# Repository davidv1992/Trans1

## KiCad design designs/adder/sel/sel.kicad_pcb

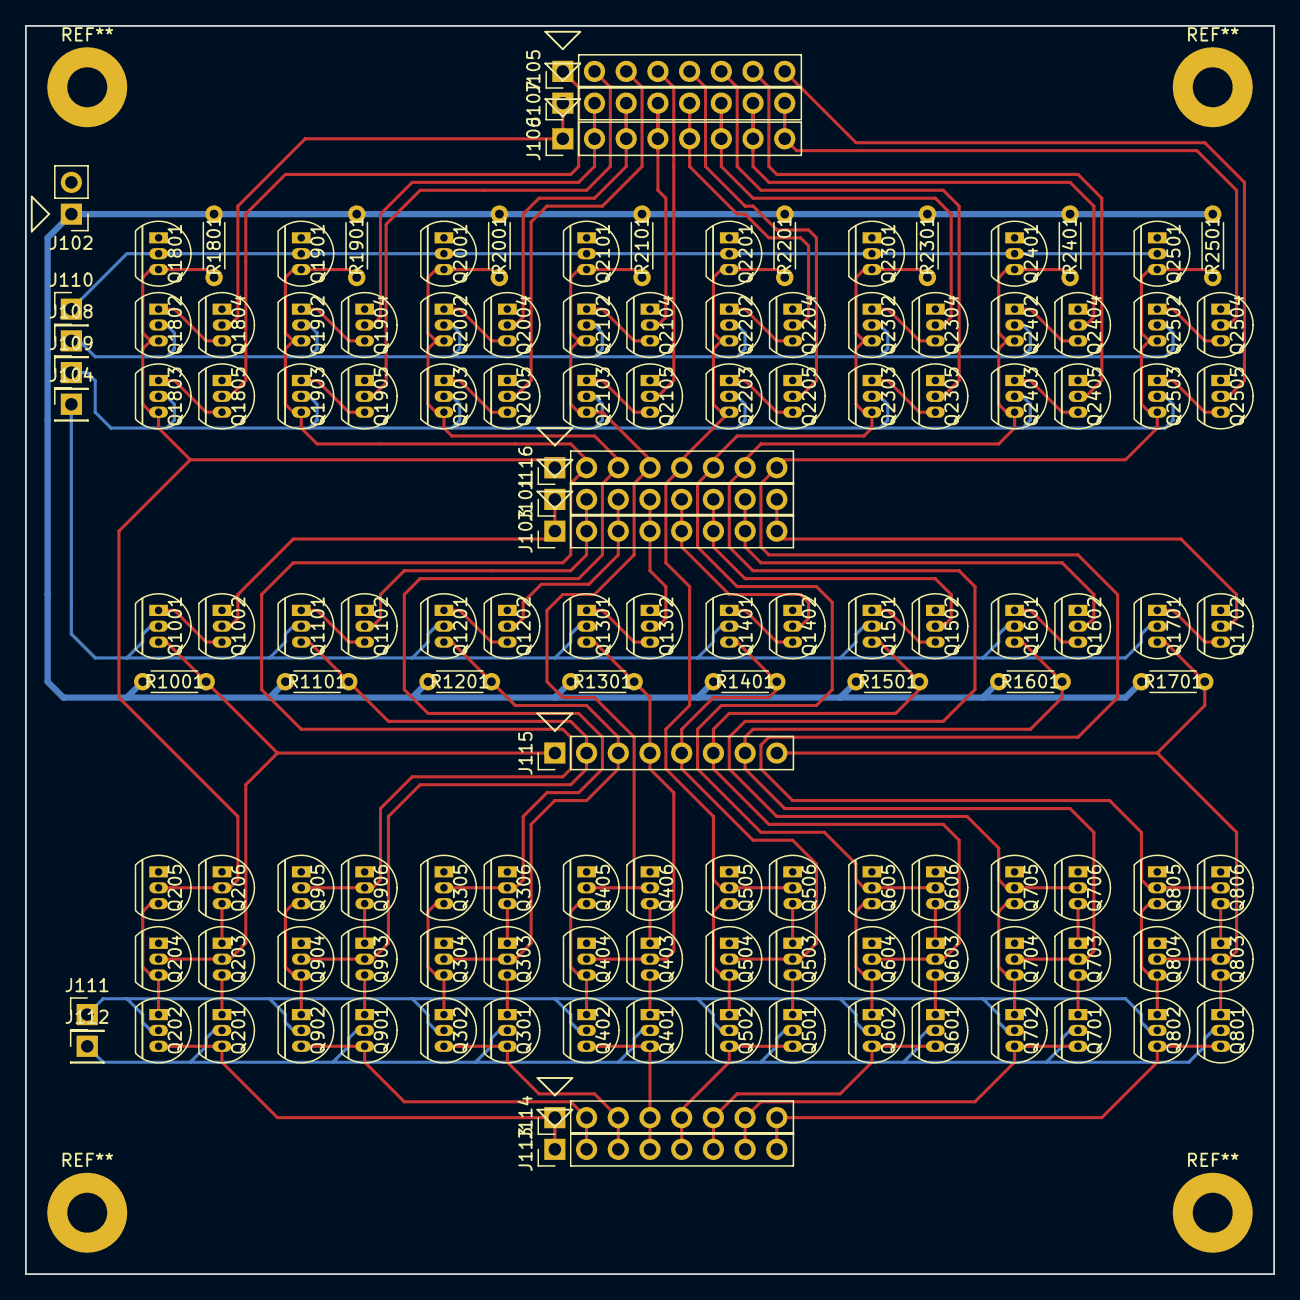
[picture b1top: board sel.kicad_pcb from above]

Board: 2 copper layers, 100.0 x 100.0 mm, 136 parts (0 on the bottom side), 104 nets.

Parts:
J101, J103, J105, J106, J107, J113, J114, J115, J116: Conn_01x08; PH_1x8
J102: Conn_01x02_Power; PH_1x2
J104, J108, J109, J110, J111, J112: Conn_01x01; PH_1x1
Q201, Q202, Q203, Q204, Q205, Q206, Q301, Q302, Q303, Q304, Q305, Q306, Q401, Q402, Q403, Q404, Q405, Q406, Q501, Q502, Q503, Q504, Q505, Q506, Q601, Q602, Q603, Q604, Q605, Q606, Q701, Q702, Q703, Q704, Q705, Q706, Q801, Q802, Q803, Q804, Q805, Q806, Q901, Q902, Q903, Q904, Q905, Q906, Q1001, Q1002, Q1101, Q1102, Q1201, Q1202, Q1301, Q1302, Q1401, Q1402, Q1501, Q1502, Q1601, Q1602, Q1701, Q1702, Q1801, Q1802, Q1803, Q1804, Q1805, Q1901, Q1902, Q1903, Q1904, Q1905, Q2001, Q2002, Q2003, Q2004, Q2005, Q2101, Q2102, Q2103, Q2104, Q2105, Q2201, Q2202, Q2203, Q2204, Q2205, Q2301, Q2302, Q2303, Q2304, Q2305, Q2401, Q2402, Q2403, Q2404, Q2405, Q2501, Q2502, Q2503, Q2504, Q2505: 2N7000; TO-92-FET
R1001, R1101, R1201, R1301, R1401, R1501, R1601, R1701, R1801, R1901, R2001, R2101, R2201, R2301, R2401, R2501: R; R_small

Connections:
/Asel0/A: J101.1, J103.1, Q1002.2
/Asel0/Aen: J104.1, Q1001.2, Q1101.2, Q1201.2, Q1301.2, Q1401.2, Q1501.2, Q1601.2, Q1701.2
/Asel0/Asel: J115.1, Q203.2, Q204.2, Q1001.3, R1001.2
/Asel1/A: J101.2, J103.2, Q1102.2
/Asel1/Asel: J115.2, Q903.2, Q904.2, Q1101.3, R1101.2
/Asel2/A: J101.3, J103.3, Q1202.2
/Asel2/Asel: J115.3, Q303.2, Q304.2, Q1201.3, R1201.2
/Asel3/A: J101.4, J103.4, Q1302.2
/Asel3/Asel: J115.4, Q403.2, Q404.2, Q1301.3, R1301.2
/Asel4/A: J101.5, J103.5, Q1402.2
/Asel4/Asel: J115.5, Q503.2, Q504.2, Q1401.3, R1401.2
/Asel5/A: J101.6, J103.6, Q1502.2
/Asel5/Asel: J115.6, Q603.2, Q604.2, Q1501.3, R1501.2
/Asel6/A: J101.7, J103.7, Q1602.2
/Asel6/Asel: J115.7, Q703.2, Q704.2, Q1601.3, R1601.2
/Asel7/A: J101.8, J103.8, Q1702.2
/Asel7/Asel: J115.8, Q803.2, Q804.2, Q1701.3, R1701.2
/Bsel0/1en: J110.1, Q1801.2, Q1901.2, Q2001.2, Q2101.2, Q2201.2, Q2301.2, Q2401.2, Q2501.2
/Bsel0/B: J106.1, J107.1, Q1804.2
/Bsel0/Ben: J108.1, Q1802.2, Q1902.2, Q2002.2, Q2102.2, Q2202.2, Q2302.2, Q2402.2, Q2502.2
/Bsel0/Out: J116.1, Q205.2, Q206.2, Q1801.3, Q1802.3, Q1803.3, R1801.2
/Bsel0/~B~: J105.1, Q1805.2
/Bsel0/~B~en: J109.1, Q1803.2, Q1903.2, Q2003.2, Q2103.2, Q2203.2, Q2303.2, Q2403.2, Q2503.2
/Bsel1/B: J106.2, J107.2, Q1904.2
/Bsel1/Out: J116.2, Q905.2, Q906.2, Q1901.3, Q1902.3, Q1903.3, R1901.2
/Bsel1/~B~: J105.2, Q1905.2
/Bsel2/B: J106.3, J107.3, Q2004.2
/Bsel2/Out: J116.3, Q305.2, Q306.2, Q2001.3, Q2002.3, Q2003.3, R2001.2
/Bsel2/~B~: J105.3, Q2005.2
/Bsel3/B: J106.4, J107.4, Q2104.2
/Bsel3/Out: J116.4, Q405.2, Q406.2, Q2101.3, Q2102.3, Q2103.3, R2101.2
/Bsel3/~B~: J105.4, Q2105.2
/Bsel4/B: J106.5, J107.5, Q2204.2
/Bsel4/Out: J116.5, Q505.2, Q506.2, Q2201.3, Q2202.3, Q2203.3, R2201.2
/Bsel4/~B~: J105.5, Q2205.2
/Bsel5/B: J106.6, J107.6, Q2304.2
/Bsel5/Out: J116.6, Q605.2, Q606.2, Q2301.3, Q2302.3, Q2303.3, R2301.2
/Bsel5/~B~: J105.6, Q2305.2
/Bsel6/B: J106.7, J107.7, Q2404.2
/Bsel6/Out: J116.7, Q705.2, Q706.2, Q2401.3, Q2402.3, Q2403.3, R2401.2
/Bsel6/~B~: J105.7, Q2405.2
/Bsel7/B: J106.8, J107.8, Q2504.2
/Bsel7/Out: J116.8, Q805.2, Q806.2, Q2501.3, Q2502.3, Q2503.3, R2501.2
/Bsel7/~B~: J105.8, Q2505.2
/out0/AndSel: J111.1, Q202.2, Q302.2, Q402.2, Q502.2, Q602.2, Q702.2, Q802.2, Q902.2
/out0/OrSel: J112.1, Q201.2, Q301.2, Q401.2, Q501.2, Q601.2, Q701.2, Q801.2, Q901.2
/out0/Out: J113.1, J114.1, Q201.3, Q202.3
/out1/Out: J113.2, J114.2, Q901.3, Q902.3
/out2/Out: J113.3, J114.3, Q301.3, Q302.3
/out3/Out: J113.4, J114.4, Q401.3, Q402.3
/out4/Out: J113.5, J114.5, Q501.3, Q502.3
/out5/Out: J113.6, J114.6, Q601.3, Q602.3
/out6/Out: J113.7, J114.7, Q701.3, Q702.3
/out7/Out: J113.8, J114.8, Q801.3, Q802.3
GND: J102.2, Q204.1, Q205.1, Q206.1, Q304.1, Q305.1, Q306.1, Q404.1, Q405.1, Q406.1, Q504.1, Q505.1, Q506.1, Q604.1, Q605.1, Q606.1, Q704.1, Q705.1, Q706.1, Q804.1, Q805.1, Q806.1, Q904.1, Q905.1, Q906.1, Q1002.1, Q1102.1, Q1202.1, Q1302.1, Q1402.1, Q1502.1, Q1602.1, Q1702.1, Q1801.1, Q1804.1, Q1805.1, Q1901.1, Q1904.1, Q1905.1, Q2001.1, Q2004.1, Q2005.1, Q2101.1, Q2104.1, Q2105.1, Q2201.1, Q2204.1, Q2205.1, Q2301.1, Q2304.1, Q2305.1, Q2401.1, Q2404.1, Q2405.1, Q2501.1, Q2504.1, Q2505.1
unnamed: Q201.1, Q203.3
unnamed: Q202.1, Q204.3, Q205.3
unnamed: Q203.1, Q206.3
unnamed: Q301.1, Q303.3
unnamed: Q302.1, Q304.3, Q305.3
unnamed: Q303.1, Q306.3
unnamed: Q401.1, Q403.3
unnamed: Q402.1, Q404.3, Q405.3
unnamed: Q403.1, Q406.3
unnamed: Q501.1, Q503.3
unnamed: Q502.1, Q504.3, Q505.3
unnamed: Q503.1, Q506.3
unnamed: Q601.1, Q603.3
unnamed: Q602.1, Q604.3, Q605.3
unnamed: Q603.1, Q606.3
unnamed: Q701.1, Q703.3
unnamed: Q702.1, Q704.3, Q705.3
unnamed: Q703.1, Q706.3
unnamed: Q801.1, Q803.3
unnamed: Q802.1, Q804.3, Q805.3
unnamed: Q803.1, Q806.3
unnamed: Q901.1, Q903.3
unnamed: Q902.1, Q904.3, Q905.3
unnamed: Q903.1, Q906.3
unnamed: Q1001.1, Q1002.3
unnamed: Q1101.1, Q1102.3
unnamed: Q1201.1, Q1202.3
unnamed: Q1301.1, Q1302.3
unnamed: Q1401.1, Q1402.3
unnamed: Q1501.1, Q1502.3
unnamed: Q1601.1, Q1602.3
unnamed: Q1701.1, Q1702.3
unnamed: Q1802.1, Q1804.3
unnamed: Q1803.1, Q1805.3
unnamed: Q1902.1, Q1904.3
unnamed: Q1903.1, Q1905.3
unnamed: Q2002.1, Q2004.3
unnamed: Q2003.1, Q2005.3
unnamed: Q2102.1, Q2104.3
unnamed: Q2103.1, Q2105.3
unnamed: Q2202.1, Q2204.3
unnamed: Q2203.1, Q2205.3
unnamed: Q2302.1, Q2304.3
unnamed: Q2303.1, Q2305.3
unnamed: Q2402.1, Q2404.3
unnamed: Q2403.1, Q2405.3
unnamed: Q2502.1, Q2504.3
unnamed: Q2503.1, Q2505.3
VCC: J102.1, R1001.1, R1101.1, R1201.1, R1301.1, R1401.1, R1501.1, R1601.1, R1701.1, R1801.1, R1901.1, R2001.1, R2101.1, R2201.1, R2301.1, R2401.1, R2501.1

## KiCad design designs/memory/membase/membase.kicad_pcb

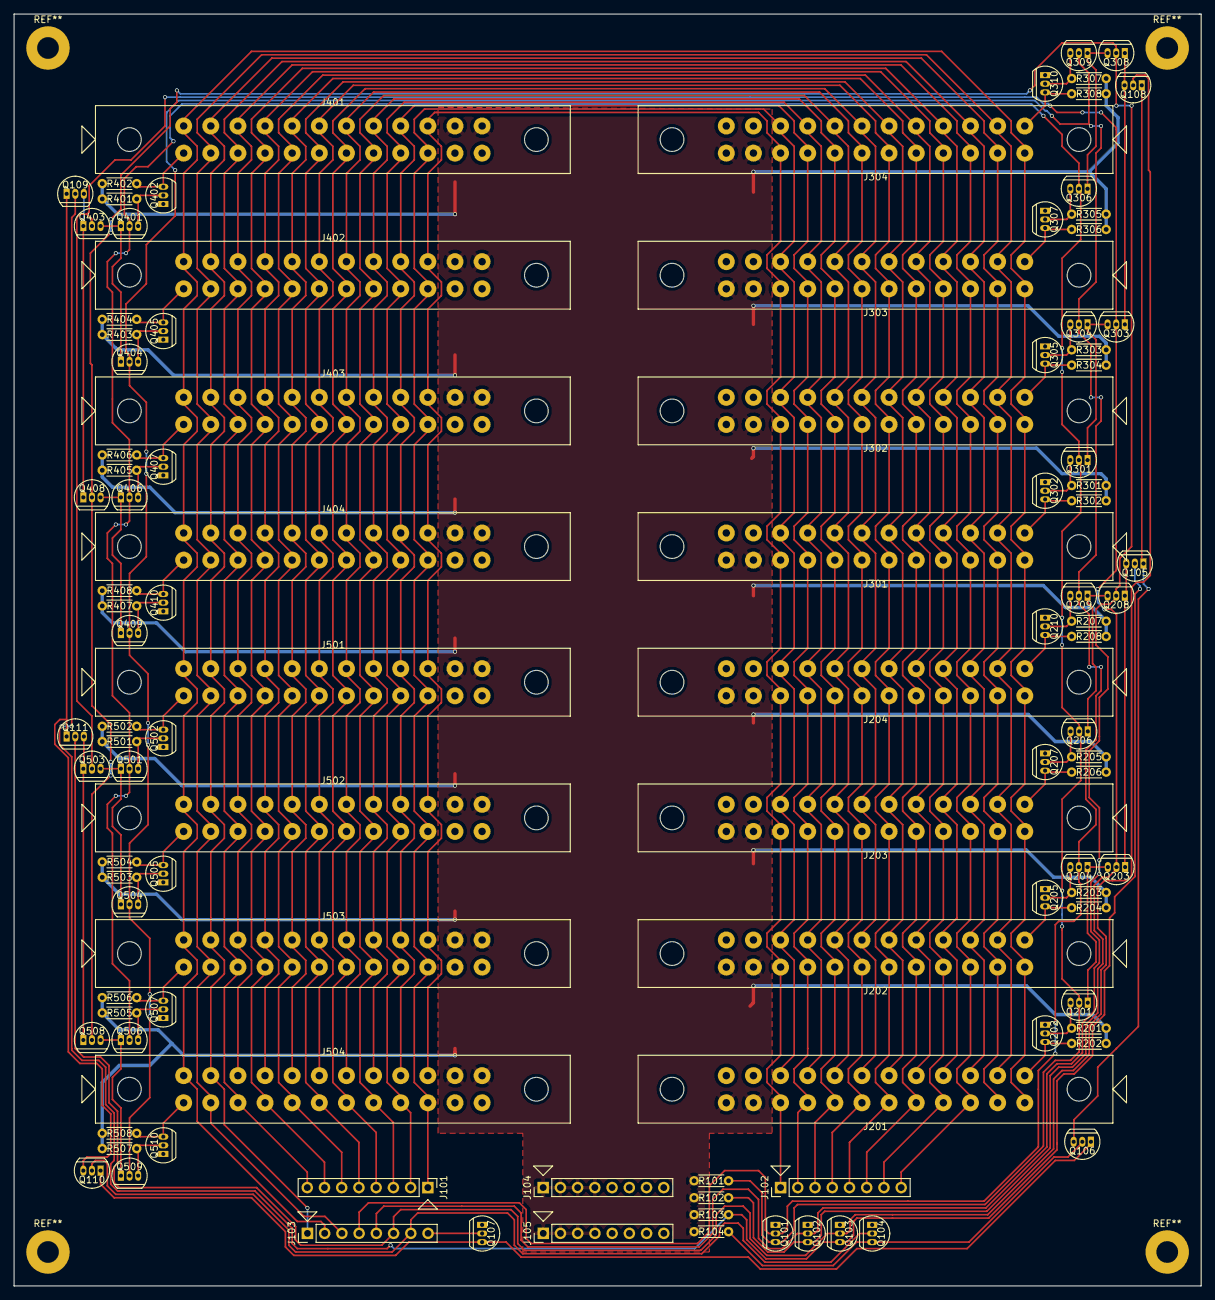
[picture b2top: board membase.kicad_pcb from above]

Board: 2 copper layers, 175.0 x 187.5 mm, 108 parts (0 on the bottom side), 77 nets.

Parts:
J101, J102, J103, J104, J105: Conn_01x08; PH_1x8
J201, J202, J203, J204, J301, J302, J303, J304, J401, J402, J403, J404, J501, J502, J503, J504: cardedge_conn; cardedge_conn_12p
Q101, Q102, Q103, Q104, Q105, Q106, Q107, Q108, Q109, Q110, Q111, Q201, Q202, Q203, Q204, Q205, Q206, Q207, Q208, Q209, Q210, Q301, Q302, Q303, Q304, Q305, Q306, Q307, Q308, Q309, Q310, Q401, Q402, Q403, Q404, Q405, Q406, Q407, Q408, Q409, Q410, Q501, Q502, Q503, Q504, Q505, Q506, Q507, Q508, Q509, Q510: 2N7000; TO-92-FET
R101, R102, R103, R104, R201, R202, R203, R204, R205, R206, R207, R208, R301, R302, R303, R304, R305, R306, R307, R308, R401, R402, R403, R404, R405, R406, R407, R408, R501, R502, R503, R504, R505, R506, R507, R508: 1k; R_small

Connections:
/connectors_1/A0: J103.1, J201.11, J202.11, J203.11, J204.11, J301.11, J302.11, J303.11, J304.11, J401.11, J402.11, J403.11, J404.11, J501.11, J502.11, J503.11, J504.11
/connectors_1/A1: J103.2, J201.12, J202.12, J203.12, J204.12, J301.12, J302.12, J303.12, J304.12, J401.12, J402.12, J403.12, J404.12, J501.12, J502.12, J503.12, J504.12
/connectors_1/A2: J103.3, J201.23, J202.23, J203.23, J204.23, J301.23, J302.23, J303.23, J304.23, J401.23, J402.23, J403.23, J404.23, J501.23, J502.23, J503.23, J504.23
/connectors_1/A3: J103.4, Q101.2, Q204.2, Q209.2, Q304.2, Q309.2, Q404.2, Q409.2, Q504.2, Q509.2
/connectors_1/A4: J103.5, Q102.2, Q208.2, Q308.2, Q408.2, Q508.2
/connectors_1/D0: J101.1, J201.15, J202.15, J203.15, J204.15, J301.15, J302.15, J303.15, J304.15, J401.15, J402.15, J403.15, J404.15, J501.15, J502.15, J503.15, J504.15
/connectors_1/D1: J101.2, J201.16, J202.16, J203.16, J204.16, J301.16, J302.16, J303.16, J304.16, J401.16, J402.16, J403.16, J404.16, J501.16, J502.16, J503.16, J504.16
/connectors_1/D2: J101.3, J201.17, J202.17, J203.17, J204.17, J301.17, J302.17, J303.17, J304.17, J401.17, J402.17, J403.17, J404.17, J501.17, J502.17, J503.17, J504.17
/connectors_1/D3: J101.4, J201.18, J202.18, J203.18, J204.18, J301.18, J302.18, J303.18, J304.18, J401.18, J402.18, J403.18, J404.18, J501.18, J502.18, J503.18, J504.18
/connectors_1/D4: J101.5, J201.19, J202.19, J203.19, J204.19, J301.19, J302.19, J303.19, J304.19, J401.19, J402.19, J403.19, J404.19, J501.19, J502.19, J503.19, J504.19
/connectors_1/D5: J101.6, J201.20, J202.20, J203.20, J204.20, J301.20, J302.20, J303.20, J304.20, J401.20, J402.20, J403.20, J404.20, J501.20, J502.20, J503.20, J504.20
/connectors_1/D6: J101.7, J201.21, J202.21, J203.21, J204.21, J301.21, J302.21, J303.21, J304.21, J401.21, J402.21, J403.21, J404.21, J501.21, J502.21, J503.21, J504.21
/connectors_1/D7: J101.8, J201.22, J202.22, J203.22, J204.22, J301.22, J302.22, J303.22, J304.22, J401.22, J402.22, J403.22, J404.22, J501.22, J502.22, J503.22, J504.22
/connectors_1/E: Q105.3, Q203.1, Q208.1
/connectors_1/~A3: Q101.3, Q201.2, Q206.2, Q301.2, Q306.2, Q401.2, Q406.2, Q501.2, Q506.2, R101.2
/connectors_1/~A4: Q102.3, Q203.2, Q303.2, Q403.2, Q503.2, R102.2
/connectors_1/~D0: J102.1, J201.3, J202.3, J203.3, J204.3, J301.3, J302.3, J303.3, J304.3, J401.3, J402.3, J403.3, J404.3, J501.3, J502.3, J503.3, J504.3
/connectors_1/~D1: J102.2, J201.4, J202.4, J203.4, J204.4, J301.4, J302.4, J303.4, J304.4, J401.4, J402.4, J403.4, J404.4, J501.4, J502.4, J503.4, J504.4
/connectors_1/~D2: J102.3, J201.5, J202.5, J203.5, J204.5, J301.5, J302.5, J303.5, J304.5, J401.5, J402.5, J403.5, J404.5, J501.5, J502.5, J503.5, J504.5
/connectors_1/~D3: J102.4, J201.6, J202.6, J203.6, J204.6, J301.6, J302.6, J303.6, J304.6, J401.6, J402.6, J403.6, J404.6, J501.6, J502.6, J503.6, J504.6
/connectors_1/~D4: J102.5, J201.7, J202.7, J203.7, J204.7, J301.7, J302.7, J303.7, J304.7, J401.7, J402.7, J403.7, J404.7, J501.7, J502.7, J503.7, J504.7
/connectors_1/~D5: J102.6, J201.8, J202.8, J203.8, J204.8, J301.8, J302.8, J303.8, J304.8, J401.8, J402.8, J403.8, J404.8, J501.8, J502.8, J503.8, J504.8
/connectors_1/~D6: J102.7, J201.9, J202.9, J203.9, J204.9, J301.9, J302.9, J303.9, J304.9, J401.9, J402.9, J403.9, J404.9, J501.9, J502.9, J503.9, J504.9
/connectors_1/~D7: J102.8, J201.10, J202.10, J203.10, J204.10, J301.10, J302.10, J303.10, J304.10, J401.10, J402.10, J403.10, J404.10, J501.10, J502.10, J503.10, J504.10
/connectors_2/E: Q108.3, Q303.1, Q308.1
/connectors_3/E: Q109.3, Q403.1, Q408.1
/connectors_4/E: Q111.3, Q503.1, Q508.1
GND: J104.5, J104.6, J104.7, J104.8, J105.5, J105.6, J105.7, J105.8, J201.13, J201.14, J202.13, J202.14, J203.13, J203.14, J204.13, J204.14, J301.13, J301.14, J302.13, J302.14, J303.13, J303.14, J304.13, J304.14, J401.13, J401.14, J402.13, J402.14, J403.13, J403.14, J404.13, J404.14, J501.13, J501.14, J502.13, J502.14, J503.13, J503.14, J504.13, J504.14, Q101.1, Q102.1, Q103.1, Q104.1, Q107.1, Q202.1, Q205.1, Q207.1, Q210.1, Q302.1, Q305.1, Q307.1, Q310.1, Q402.1, Q405.1, Q407.1, Q410.1, Q502.1, Q505.1, Q507.1, Q510.1
unnamed: J103.6, Q103.2, Q108.2, Q111.2
unnamed: J103.7, Q104.2, Q110.2
unnamed: J103.8, Q107.2
unnamed: J201.24, Q202.3, R202.2
unnamed: J202.24, Q205.3, R204.2
unnamed: J203.24, Q207.3, R206.2
unnamed: J204.24, Q210.3, R208.2
unnamed: J301.24, Q302.3, R302.2
unnamed: J302.24, Q305.3, R304.2
unnamed: J303.24, Q307.3, R306.2
unnamed: J304.24, Q310.3, R308.2
unnamed: J401.24, Q402.3, R402.2
unnamed: J402.24, Q405.3, R404.2
unnamed: J403.24, Q407.3, R406.2
unnamed: J404.24, Q410.3, R408.2
unnamed: J501.24, Q502.3, R502.2
unnamed: J502.24, Q505.3, R504.2
unnamed: J503.24, Q507.3, R506.2
unnamed: J504.24, Q510.3, R508.2
unnamed: Q103.3, Q105.2, Q109.2, R103.2
unnamed: Q104.3, Q106.2, R104.2
unnamed: Q105.1, Q106.3, Q108.1
unnamed: Q106.1, Q107.3, Q110.1
unnamed: Q109.1, Q110.3, Q111.1
unnamed: Q201.1, Q203.3, Q204.1
unnamed: Q201.3, Q202.2, R201.2
unnamed: Q204.3, Q205.2, R203.2
unnamed: Q206.1, Q208.3, Q209.1
unnamed: Q206.3, Q207.2, R205.2
unnamed: Q209.3, Q210.2, R207.2
unnamed: Q301.1, Q303.3, Q304.1
unnamed: Q301.3, Q302.2, R301.2
unnamed: Q304.3, Q305.2, R303.2
unnamed: Q306.1, Q308.3, Q309.1
unnamed: Q306.3, Q307.2, R305.2
unnamed: Q309.3, Q310.2, R307.2
unnamed: Q401.1, Q403.3, Q404.1
unnamed: Q401.3, Q402.2, R401.2
unnamed: Q404.3, Q405.2, R403.2
unnamed: Q406.1, Q408.3, Q409.1
unnamed: Q406.3, Q407.2, R405.2
unnamed: Q409.3, Q410.2, R407.2
unnamed: Q501.1, Q503.3, Q504.1
unnamed: Q501.3, Q502.2, R501.2
unnamed: Q504.3, Q505.2, R503.2
unnamed: Q506.1, Q508.3, Q509.1
unnamed: Q506.3, Q507.2, R505.2
unnamed: Q509.3, Q510.2, R507.2
VCC: J104.1, J104.2, J104.3, J104.4, J105.1, J105.2, J105.3, J105.4, J201.1, J201.2, J202.1, J202.2, J203.1, J203.2, J204.1, J204.2, J301.1, J301.2, J302.1, J302.2, J303.1, J303.2, J304.1, J304.2, J401.1, J401.2, J402.1, J402.2, J403.1, J403.2, J404.1, J404.2, J501.1, J501.2, J502.1, J502.2, J503.1, J503.2, J504.1, J504.2, R101.1, R102.1, R103.1, R104.1, R201.1, R202.1, R203.1, R204.1, R205.1, R206.1, R207.1, R208.1, R301.1, R302.1, R303.1, R304.1, R305.1, R306.1, R307.1, R308.1, R401.1, R402.1, R403.1, R404.1, R405.1, R406.1, R407.1, R408.1, R501.1, R502.1, R503.1, R504.1, R505.1, R506.1, R507.1, R508.1
